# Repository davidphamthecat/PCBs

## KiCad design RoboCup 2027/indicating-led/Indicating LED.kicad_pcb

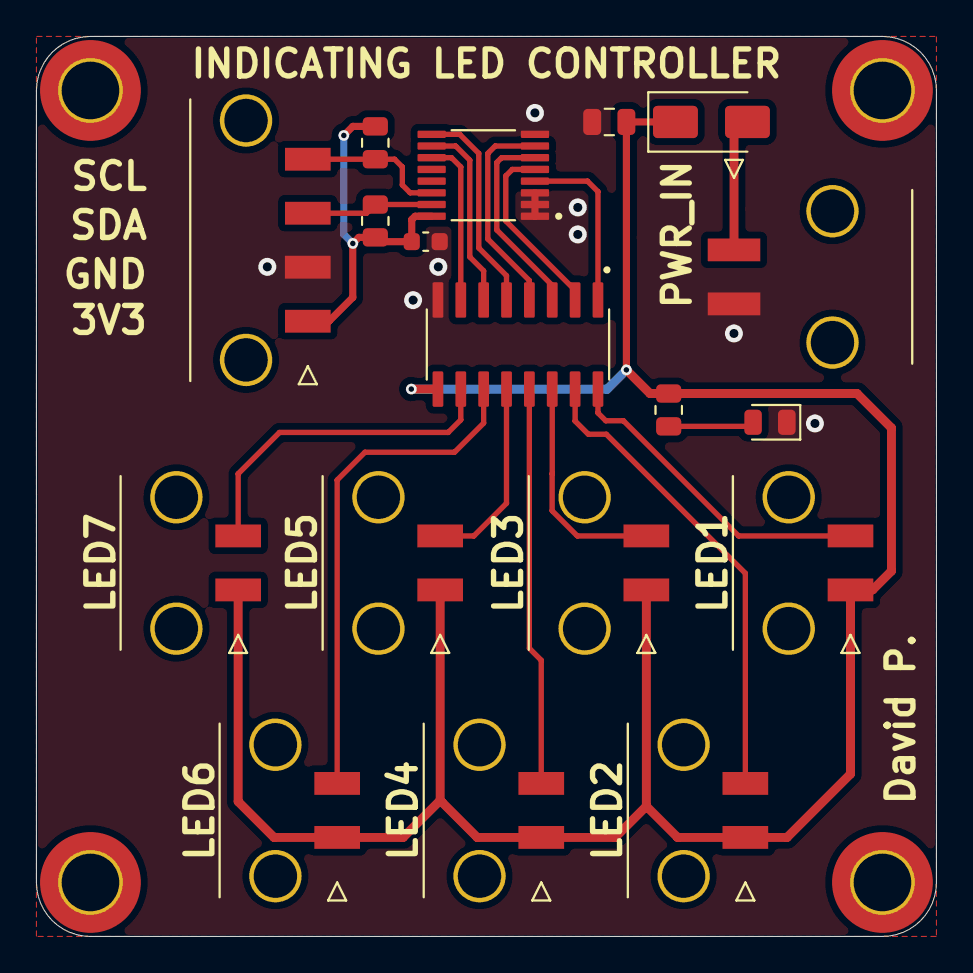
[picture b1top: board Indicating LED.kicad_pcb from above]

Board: 2 copper layers, 50.0 x 50.0 mm, 22 parts (0 on the bottom side), 21 nets.

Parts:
C101: 0.1u; C_0603_1608Metric
C102: 10u; C_0805_2012Metric
D101: LED; LED_0805_2012Metric
D102: SS14; D_SMA
H101, H102, H103, H104: MountingHole_M3; MountingHole_3.2mm_M3_DIN965_Pad_TopBottom
J101: Signal; CONN_Molex-MicroFit-01x04_Vertical
J102: PWR_In; CONN_Molex-MicroFit-01x02_Horizontal
J103, J104, J105, J106, J107, J108, J109: Conn_PWR; CONN_Molex-MicroFit-01x02_Vertical
R101, R102, R103: 4k7; R_0805_2012Metric
U101: TCA9534; IC-TCA9534PWR
U102: IC_ULN2003A; IC-ULN2003A

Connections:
+12V: C102.1, D102.1 (K), J103.+ (Pin_1), J104.+ (Pin_1), J105.+ (Pin_1), J106.+ (Pin_1), J107.+ (Pin_1), J108.+ (Pin_1), J109.+ (Pin_1), R101.2, U102.9 (COM)
/LED1-pwr: J103.- (Pin_2), U102.16 (1C)
/LED1-sig: U101.4 (P0), U102.1 (1B)
/LED2-pwr: J104.- (Pin_2), U102.15 (2C)
/LED2-sig: U101.5 (P1), U102.2 (2B)
/LED3-pwr: J105.- (Pin_2), U102.14 (3C)
/LED3-sig: U101.6 (P2), U102.3 (3B)
/LED4-pwr: J106.- (Pin_2), U102.13 (4C)
/LED4-sig: U101.7 (P3), U102.4 (4B)
/LED5-pwr: J107.- (Pin_2), U102.12 (5C)
/LED5-sig: U101.9 (P4), U102.5 (5B)
/LED6-pwr: J108.- (Pin_2), U102.11 (6C)
/LED6-sig: U101.10 (P5), U102.6 (6B)
/LED7-pwr: J109.- (Pin_2), U102.10 (7C)
/LED7-sig: U101.11 (P6), U102.7 (7B)
/SCL: J101.4, R103.1, U101.14 (SCL)
/SDA: J101.3, R102.1, U101.15 (SDA)
GND: C101.2, C102.2, D101.1, J101.2, J102.- (Pin_2), U101.1 (A0), U101.2 (A1), U101.3 (A2), U101.8 (GND), U102.8 (E)
unnamed: D101.2, R101.1
unnamed: D102.2 (A), J102.+ (Pin_1)
VCC: C101.1, J101.1, R102.2, R103.2, U101.16 (VDD)

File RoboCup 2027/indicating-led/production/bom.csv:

Designator,Footprint,Quantity,Value,LCSC Part #
C101,0603,1,0.1u,C14663
C102,0805,1,10u,C15850
D101,0805,1,LED,C84256
D102,D_SMA,1,SS14,C2480
"H101, H102, H103, H104",MountingHole_3.2mm_M3_DIN965_Pad_TopBottom,4,MountingHole_M3,DNP
J101,CONN_Molex-MicroFit-01x04_Vertical,1,Signal,
J102,CONN_Molex-MicroFit-01x02_Horizontal,1,PWR_In,
"J103, J104, J105, J106, J107, J108, J109",CONN_Molex-MicroFit-01x02_Vertical,7,Conn_PWR,
"R101, R102, R103",0805,3,4k7,C17673
U101,IC-TCA9534PWR,1,TCA9534,C783615
U102,IC-ULN2003A,1,IC_ULN2003A,C7512

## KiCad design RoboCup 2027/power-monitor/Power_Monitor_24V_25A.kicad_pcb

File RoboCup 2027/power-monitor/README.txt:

heloooo, remember when ordering select 2 oz copper

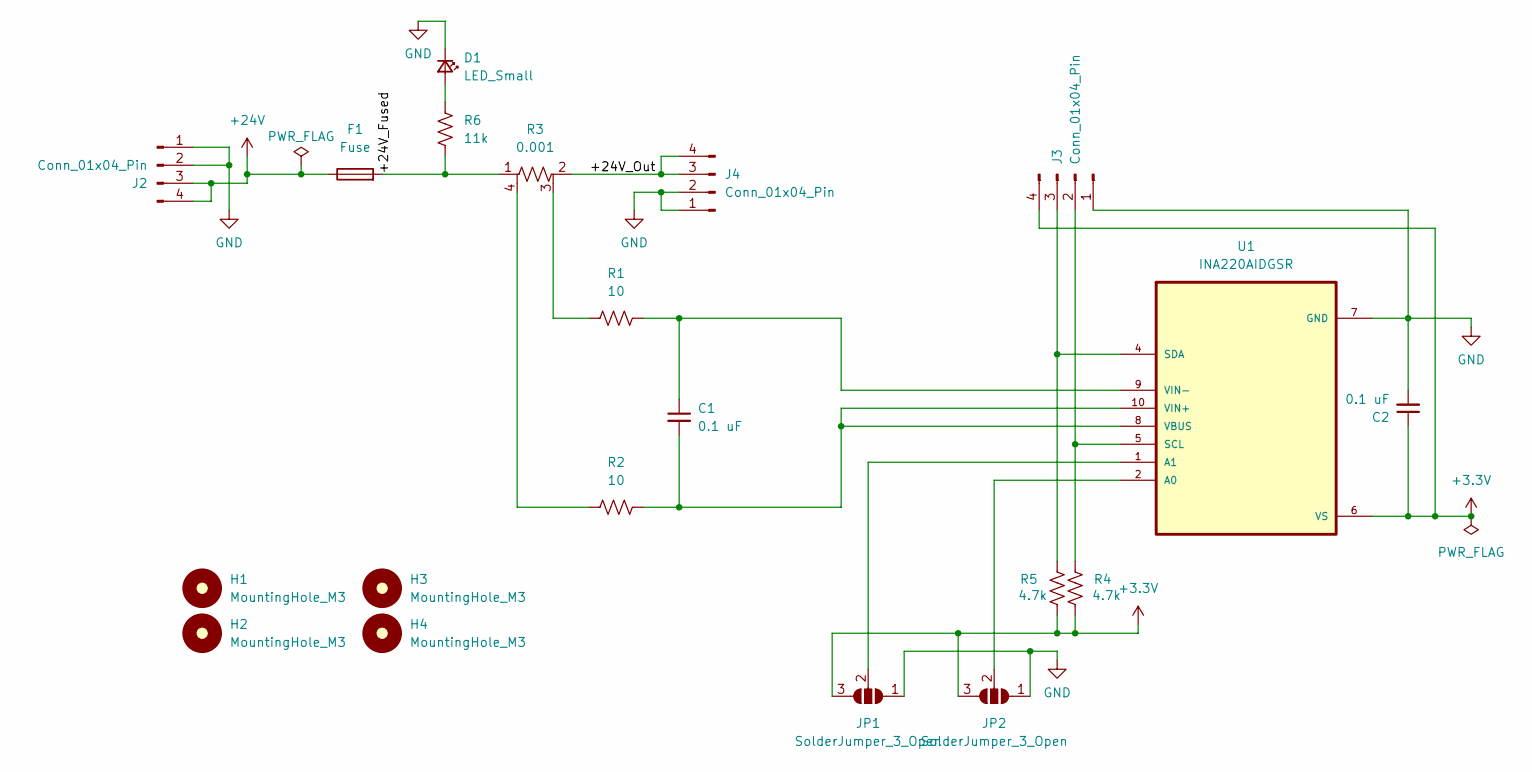
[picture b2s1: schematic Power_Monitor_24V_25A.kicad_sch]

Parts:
C1, C2: 0.1 uF; C_0603_1608Metric
D1: LED_Small; LED_0805_2012Metric
F1: Fuse; Fuseholder_Blade_Mini_Keystone_3568
H1, H2, H3, H4: MountingHole_M3; MountingHole_3.2mm_M3
J2, J3, J4: Conn_01x04_Pin; Molex_Mega-Fit_76829-0004_2x02_P5.70mm_Vertical
JP1, JP2: SolderJumper_3_Open; SolderJumper-3_P1.3mm_Open_RoundedPad1.0x1.5mm
R1, R2: 10; R_0603_1608Metric
R3: 0.001; RESCAF_LVK25-4
R4, R5: 4.7k; R_0603_1608Metric
R6: 11k; R_0603_1608Metric
U1: INA220AIDGSR; SOP50P490X110-10N

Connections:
+3.3V: C2.1, J3.4, JP1.3 (B), JP2.3 (B), R4.1, R5.1, U1.6 (VS)
+24V: F1.1, J2.3, J2.4
/+24V_Fused: F1.2, R3.1, R6.1
/+24V_Out: J4.3, J4.4, R3.2
GND: C2.2, D1.1 (K), J2.1, J2.2, J3.1, J4.1, J4.2, JP1.1 (A), JP2.1 (A), U1.7 (GND)
unnamed: D1.2 (A), R6.2
unnamed: J3.2, R4.2, U1.5 (SCL)
unnamed: J3.3, R5.2, U1.4 (SDA)
unnamed: JP1.2 (C), U1.1 (A1)
unnamed: JP2.2 (C), U1.2 (A0)
unnamed: R1.1, R3.3
unnamed: R2.1, R3.4
unnamed: C1.2, R2.2, U1.8 (VBUS), U1.10 (VIN+)
unnamed: C1.1, R1.2, U1.9 (VIN-)

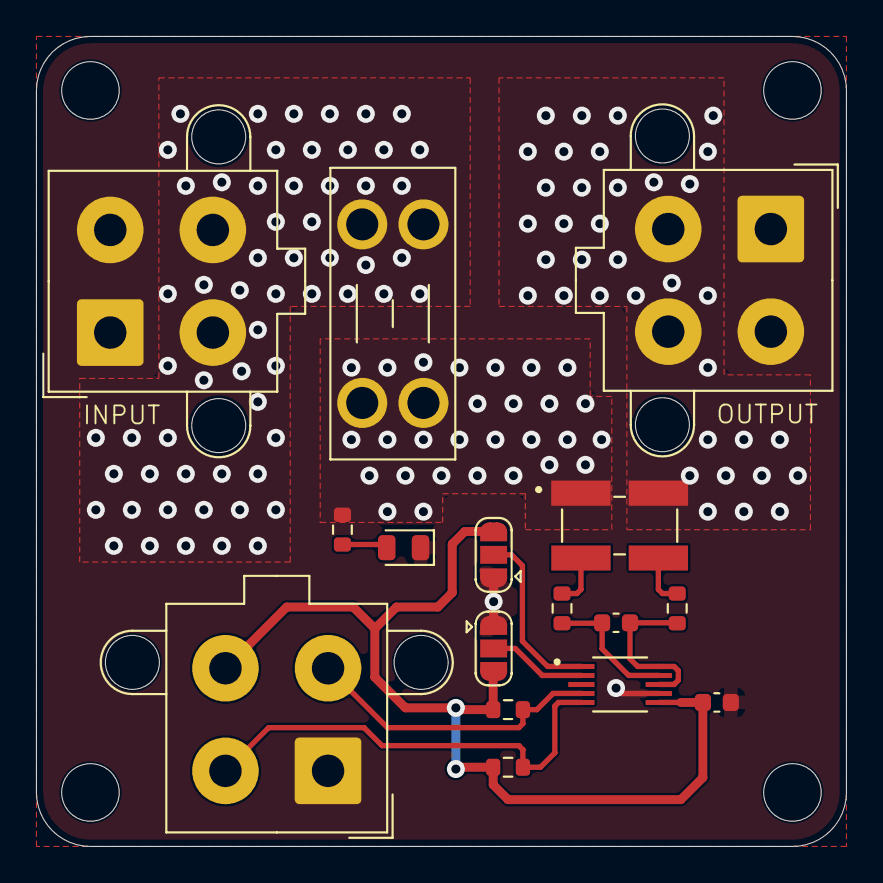
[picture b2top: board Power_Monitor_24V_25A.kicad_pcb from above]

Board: 2 copper layers, 45.0 x 45.0 mm, 20 parts (0 on the bottom side), 14 nets.

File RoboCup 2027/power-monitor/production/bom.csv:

Designator,Footprint,Quantity,Value,LCSC Part #
"C1, C2",0603,2,0.1 uF,
D1,0805,1,LED_Small,
F1,Fuseholder_Blade_Mini_Keystone_3568,1,Fuse,
"H1, H2, H3, H4",MountingHole_3.2mm_M3,4,MountingHole_M3,
"J2, J3, J4",Molex_Mega-Fit_76829-0004_2x02_P5.70mm_Vertical,3,Conn_01x04_Pin,
"R1, R2",0603,2,10,
R3,RESCAF_LVK25-4,1,0.001,
"R4, R5",0603,2,4.7k,
R6,0603,1,11k,
U1,SOP50P490X110-10N,1,INA220AIDGSR,

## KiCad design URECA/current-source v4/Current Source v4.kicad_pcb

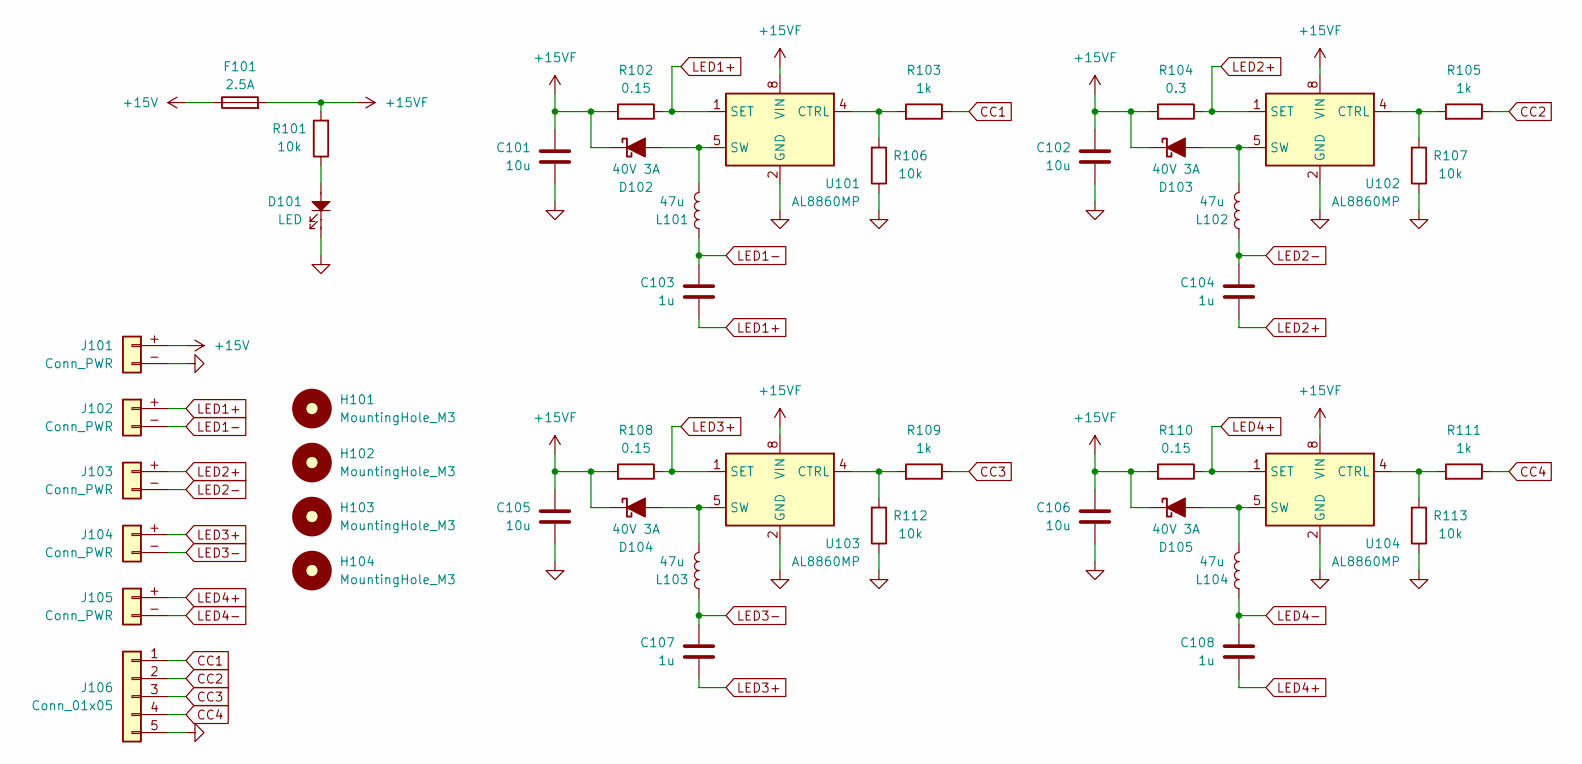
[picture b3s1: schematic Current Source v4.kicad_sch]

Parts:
C101, C102, C105, C106: 10u; C_1206_3216Metric; Part Type Basic; LCSC C70462
C103, C104, C107, C108: 1u; C_0603_1608Metric; Part Type Basic; LCSC C15849
D101: LED; LED_0805_2012Metric; Part Type Basic; LCSC C84256
D102, D103, D104, D105: 40V 3A; D_SMA; Part Type Extended; LCSC C8678
F101: 2.5A; FUSE-MCCQ-122; LCSC DNP
H101, H102, H103, H104: MountingHole_M3; MountingHole_3.2mm_M3_DIN965_Pad_TopBottom; LCSC DNP
J101: Conn_PWR; CONN_XT30U-F_Vertical; LCSC DNP
J102, J103, J104, J105: Conn_PWR; CONN_JST_XH_B2B-XH-AM_1x02_P2.50mm_Vertical; LCSC DNP
J106: Conn_01x05; PinHeader_1x05_P2.54mm_Vertical; LCSC DNP
L101, L102, L103, L104: 47u; L_10.1x10.1_H4.5; Part Type Extended; LCSC C163611
R101, R106, R107, R112, R113: 10k; R_0603_1608Metric; Part Type Basic; LCSC C25804
R102, R108, R110: 0.15; R_1206_3216Metric; Part Type Extended; LCSC C37936
R103, R105, R109, R111: 1k; R_0603_1608Metric; Part Type Basic; LCSC C21190
R104: 0.3; R_1206_3216Metric; Part Type Extended; LCSC C59882
U101, U102, U103, U104: AL8860MP; MSOP-8-1EP_3x3mm_P0.65mm_EP1.5x1.8mm; Part Type Extended; LCSC C500782

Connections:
+15V: F101.1, J101.+ (Pin_1)
+15VF: C101.1, C102.1, C105.1, C106.1, D102.1 (K), D103.1 (K), D104.1 (K), D105.1 (K), F101.2, R101.2, R102.2, R104.2, R108.2, R110.2, U101.8 (VIN), U102.8 (VIN), U103.8 (VIN), U104.8 (VIN)
CC1: J106.1, R103.1
CC2: J106.2, R105.1
CC3: J106.3, R109.1
CC4: J106.4, R111.1
GND: C101.2, C102.2, C105.2, C106.2, D101.1, J101.- (Pin_2), J106.5, R106.1, R107.1, R112.1, R113.1, U101.2 (GND), U101.3 (GND), U101.9 (GND), U102.2 (GND), U102.3 (GND), U102.9 (GND), U103.2 (GND), U103.3 (GND), U103.9 (GND), U104.2 (GND), U104.3 (GND), U104.9 (GND)
LED1+: C103.2, J102.+ (Pin_1), R102.1, U101.1 (SET)
LED1-: C103.1, J102.- (Pin_2), L101.1
LED2+: C104.2, J103.+ (Pin_1), R104.1, U102.1 (SET)
LED2-: C104.1, J103.- (Pin_2), L102.1
LED3+: C107.2, J104.+ (Pin_1), R108.1, U103.1 (SET)
LED3-: C107.1, J104.- (Pin_2), L103.1
LED4+: C108.2, J105.+ (Pin_1), R110.1, U104.1 (SET)
LED4-: C108.1, J105.- (Pin_2), L104.1
unnamed: D101.2, R101.1
unnamed: D102.2 (A), L101.2, U101.5 (SW), U101.6 (SW)
unnamed: D103.2 (A), L102.2, U102.5 (SW), U102.6 (SW)
unnamed: D104.2 (A), L103.2, U103.5 (SW), U103.6 (SW)
unnamed: D105.2 (A), L104.2, U104.5 (SW), U104.6 (SW)
unnamed: R103.2, R106.2, U101.4 (CTRL)
unnamed: R105.2, R107.2, U102.4 (CTRL)
unnamed: R109.2, R112.2, U103.4 (CTRL)
unnamed: R111.2, R113.2, U104.4 (CTRL)

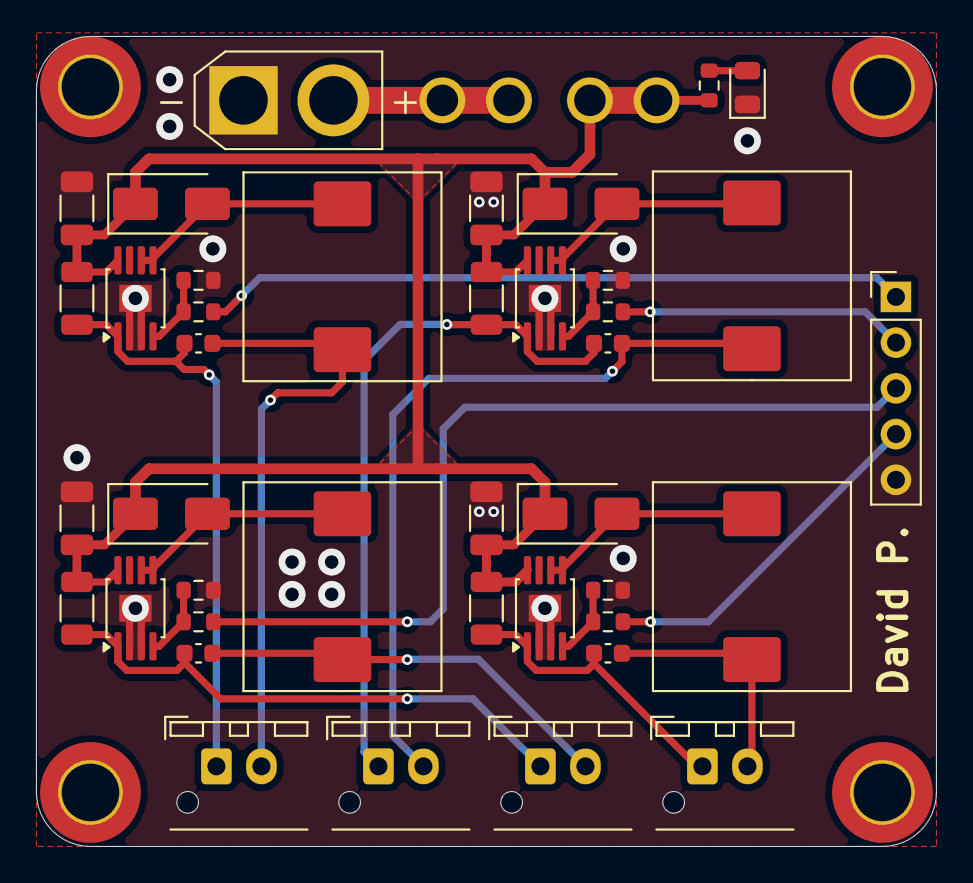
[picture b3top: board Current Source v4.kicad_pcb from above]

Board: 2 copper layers, 50.0 x 45.0 mm, 45 parts (0 on the bottom side), 24 nets.

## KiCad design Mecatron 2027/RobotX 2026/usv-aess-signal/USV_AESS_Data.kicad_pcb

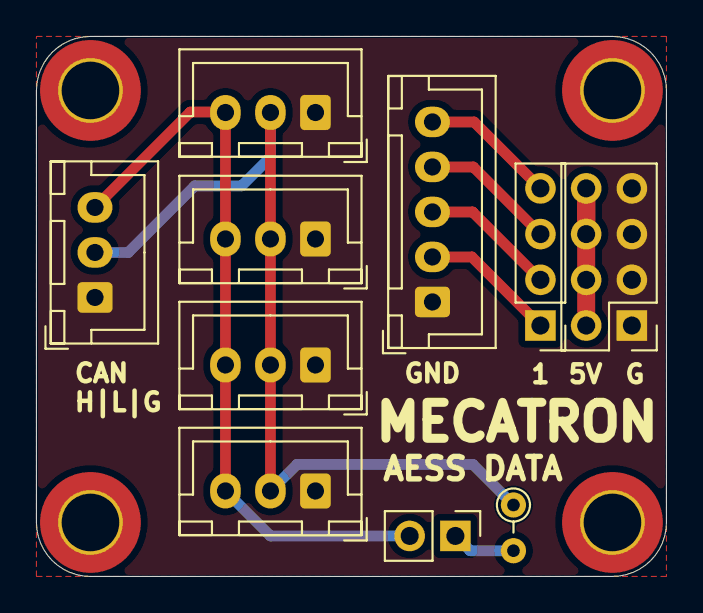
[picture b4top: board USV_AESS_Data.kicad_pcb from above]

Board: 2 copper layers, 35.0 x 30.0 mm, 14 parts (0 on the bottom side), 9 nets.

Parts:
H101, H102, H103, H104: MountingHole_M3; MountingHole_3.2mm_M3_DIN965_Pad_TopBottom
J101, J102, J103, J104, J105: CAN; JST_XH_B3B-XH-A_1x03_P2.50mm_Vertical
J106: PWM +/-; PinHeader_2x04_P2.54mm_Vertical
J107: PWM; PinHeader_1x04_P2.54mm_Vertical
J108: PWM_Out; JST_XH_B5B-XH-A_1x05_P2.50mm_Vertical
J109: Conn_01x02; PinHeader_1x02_P2.54mm_Vertical
R101: 120; R_Axial_DIN0204_L3.6mm_D1.6mm_P2.54mm_Vertical

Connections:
+5V: J106.2, J106.4, J106.6, J106.8
/CAN_H: J101.3, J102.3, J103.3, J104.3, J105.3, J109.2
/CAN_L: J101.2, J102.2, J103.2, J104.2, J105.2, R101.1
/PWM-01: J107.1, J108.2
/PWM-02: J107.2, J108.3
/PWM-03: J107.3, J108.4
/PWM-04: J107.4, J108.5
GND: J101.1, J102.1, J103.1, J104.1, J105.1, J106.1, J106.3, J106.5, J106.7, J108.1
unnamed: J109.1, R101.2

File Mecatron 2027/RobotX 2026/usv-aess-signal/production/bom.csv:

Designator,Footprint,Quantity,Value,LCSC Part #
"H101, H102, H103, H104",MountingHole_3.2mm_M3_DIN965_Pad_TopBottom,4,MountingHole_M3,
"J101, J102, J103, J104, J105",JST_XH_B3B-XH-A_1x03_P2.50mm_Vertical,5,CAN,
J106,PinHeader_2x04_P2.54mm_Vertical,1,PWM +/-,
J107,PinHeader_1x04_P2.54mm_Vertical,1,PWM,
J108,JST_XH_B5B-XH-A_1x05_P2.50mm_Vertical,1,PWM_Out,
J109,PinHeader_1x02_P2.54mm_Vertical,1,Conn_01x02,
R101,R_Axial_DIN0204_L3.6mm_D1.6mm_P2.54mm_Vertical,1,120,

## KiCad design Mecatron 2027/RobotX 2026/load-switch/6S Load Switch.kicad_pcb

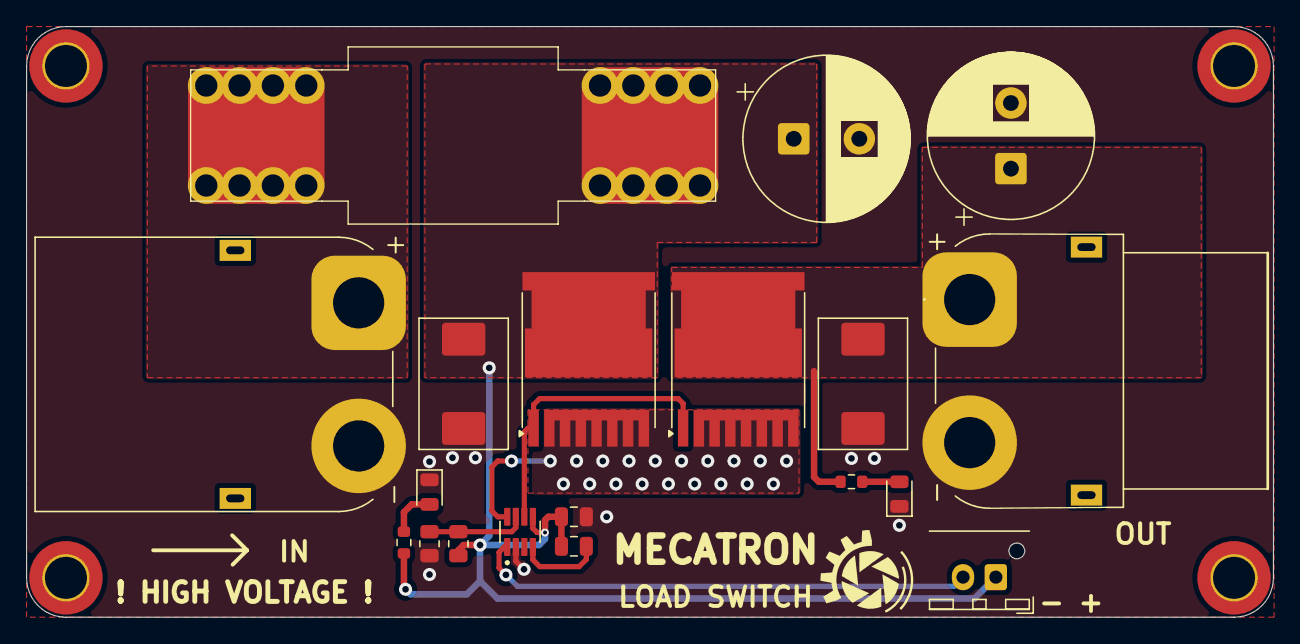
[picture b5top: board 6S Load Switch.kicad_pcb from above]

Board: 4 copper layers, 95.0 x 45.0 mm, 23 parts (0 on the bottom side), 11 nets.

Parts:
C101, C102: 620u 50V; CP_Radial_D12.5mm_P5.00mm
C103, C104: 1u; C_0805_2012Metric
D101, D102: SMCJ33CA; D_SMC_TVS
D103, D104: LED; LED_0805_2012Metric
F101: 60A; FUSE-MIDI-STANDOFF_BUTR_0850_NO_HOLE
H101, H102, H103, H104: MountingHole_M3; MountingHole_3.2mm_M3_DIN965_Pad_TopBottom
J101: XT90M; CONN_XT90PW-M_Horizontal
J102: XT90F; CONN_XT90PW-F_Horizontal
J103: Conn_EN; CONN_JST_XH_B2B-XH-AM_1x02_P2.50mm_Vertical
Q101, Q102: IPT015N10N5; Infineon_PG-HSOF-8-1
R101, R102: 5k1; R_0603_1608Metric
R103: 220k; R_0805_2012Metric
R104: 10k; R_0805_2012Metric
U101: LM74502DDFR; IC-LM74502

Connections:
+25V2: F101.1, J101.+ (Pin_1)
+25V2F: C101.1, C103.1, C104.1, D101.2 (A), F101.2, J103.+ (Pin_1), Q101.3 (D), R101.2, R103.2, U101.5 (VS)
+25V2FO: C102.1, D102.2 (A), J102.+ (Pin_1), Q102.3 (D), R102.2
/PWR_EN: J103.- (Pin_2), U101.1 (EN/UVLO)
GND: C101.2, C102.2, C104.2, D101.1 (K), D102.1 (K), D103.1, D104.1, J101.- (Pin_2), J102.- (Pin_2), R104.1, U101.2 (GND)
unnamed: D103.2, R101.1
unnamed: D104.2, R102.1
unnamed: Q101.1 (G), Q102.1 (G), U101.6 (GATE)
unnamed: Q101.2 (S), Q102.2 (S), U101.8 (SRC)
unnamed: R103.1, R104.2, U101.7 (OV)
unnamed: C103.2, U101.4 (VCAP)

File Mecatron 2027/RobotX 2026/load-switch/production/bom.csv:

Designator,Footprint,Quantity,Value,LCSC Part #
"C101, C102",CP_Radial_D12.5mm_P5.00mm,2,620u 50V,
"C103, C104",0805,2,1u,C28323
"D101, D102",D_SMC_TVS,2,SMCJ33CA,C310048
"D103, D104",0805,2,LED,C84256
F101,FUSE-MIDI-STANDOFF_BUTR_0850_NO_HOLE,1,60A,
"H101, H102, H103, H104",MountingHole_3.2mm_M3_DIN965_Pad_TopBottom,4,MountingHole_M3,
J101,CONN_XT90PW-M_Horizontal,1,XT90M,
J102,CONN_XT90PW-F_Horizontal,1,XT90F,
J103,CONN_JST_XH_B2B-XH-AM_1x02_P2.50mm_Vertical,1,Conn_EN,
"Q101, Q102",Infineon_PG-HSOF-8-1,2,IPT015N10N5,C108964
"R101, R102",0603,2,5k1,C23186
R103,0805,1,220k,C17556
R104,0805,1,10k,C17414
U101,IC-LM74502,1,LM74502DDFR,C3236215

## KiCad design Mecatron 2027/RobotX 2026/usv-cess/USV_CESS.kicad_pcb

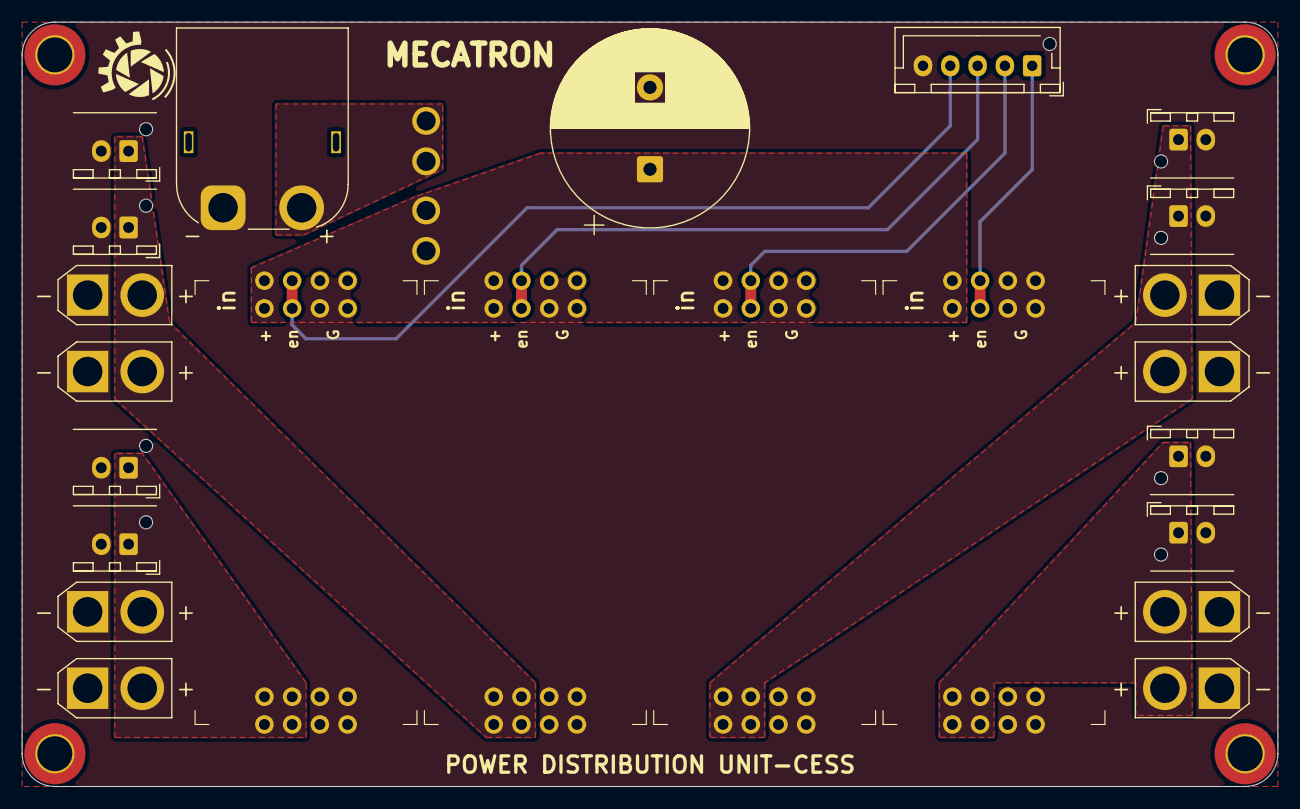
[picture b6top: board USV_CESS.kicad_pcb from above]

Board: 2 copper layers, 115.0 x 70.0 mm, 28 parts (0 on the bottom side), 11 nets.

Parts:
C101: 1000u; CP_Radial_D18.0mm_P7.50mm
F101: 40A; FUSE-MCCQ-122
H101, H102, H103, H104: MountingHole_M3; MountingHole_3.2mm_M3_DIN965_Pad_TopBottom
J101: XT60M; CONN_XT60PW-M_Horizontal
J102: EN; JST_XH_B5B-XH-AM_1x05_P2.50mm_Vertical
J103, J104, J107, J108, J111, J112, J115, J116: JST_XH; CONN_JST_XH_B2B-XH-AM_1x02_P2.50mm_Vertical
J105, J106, J109, J110, J113, J114, J117, J118: XT30; CONN_XT30U-F_Vertical
U101: Output 1; CUS-TPS54560 KangWeiTech
U102: Output 2; CUS-TPS54560 KangWeiTech
U103: Output 3; CUS-TPS54560 KangWeiTech
U104: Output 4; CUS-TPS54560 KangWeiTech

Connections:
+25V2: F101.1, J101.+ (Pin_1)
+25V2F: C101.1, F101.2, U101.1 (V_{IN}), U102.1 (V_{IN}), U103.1 (V_{IN}), U104.1 (V_{IN})
/EN_1: J102.1, U101.EN
/EN_2: J102.2, U102.EN
/EN_3: J102.3, U103.EN
/EN_4: J102.4, U104.EN
GND: C101.2, J101.- (Pin_2), J102.5, J103.- (Pin_2), J104.- (Pin_2), J105.- (Pin_2), J106.- (Pin_2), J107.- (Pin_2), J108.- (Pin_2), J109.- (Pin_2), J110.- (Pin_2), J111.- (Pin_2), J112.- (Pin_2), J113.- (Pin_2), J114.- (Pin_2), J115.- (Pin_2), J116.- (Pin_2), J117.- (Pin_2), J118.- (Pin_2), U101.G (GND), U102.G (GND), U103.G (GND), U104.G (GND)
Output 1: J103.+ (Pin_1), J104.+ (Pin_1), J105.+ (Pin_1), J106.+ (Pin_1), U101.2 (V_{OUT})
Output 2: J107.+ (Pin_1), J108.+ (Pin_1), J109.+ (Pin_1), J110.+ (Pin_1), U102.2 (V_{OUT})
Output 3: J111.+ (Pin_1), J112.+ (Pin_1), J113.+ (Pin_1), J114.+ (Pin_1), U103.2 (V_{OUT})
Output 4: J115.+ (Pin_1), J116.+ (Pin_1), J117.+ (Pin_1), J118.+ (Pin_1), U104.2 (V_{OUT})

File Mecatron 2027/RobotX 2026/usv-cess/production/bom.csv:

Designator,Footprint,Quantity,Value,LCSC Part #
C101,CP_Radial_D18.0mm_P7.50mm,1,1000u,C724666
F101,FUSE-MCCQ-122,1,40A,
"H101, H102, H103, H104",MountingHole_3.2mm_M3_DIN965_Pad_TopBottom,4,MountingHole_M3,
J101,CONN_XT60PW-M_Horizontal,1,XT60M,
J102,JST_XH_B5B-XH-AM_1x05_P2.50mm_Vertical,1,EN,
"J103, J104, J107, J108, J111, J112, J115, J116",CONN_JST_XH_B2B-XH-AM_1x02_P2.50mm_Vertical,8,JST_XH,
"J105, J106, J109, J110, J113, J114, J117, J118",CONN_XT30U-F_Vertical,8,XT30,
U101,CUS-TPS54560 KangWeiTech,1,Output 1,
U102,CUS-TPS54560 KangWeiTech,1,Output 2,
U103,CUS-TPS54560 KangWeiTech,1,Output 3,
U104,CUS-TPS54560 KangWeiTech,1,Output 4,

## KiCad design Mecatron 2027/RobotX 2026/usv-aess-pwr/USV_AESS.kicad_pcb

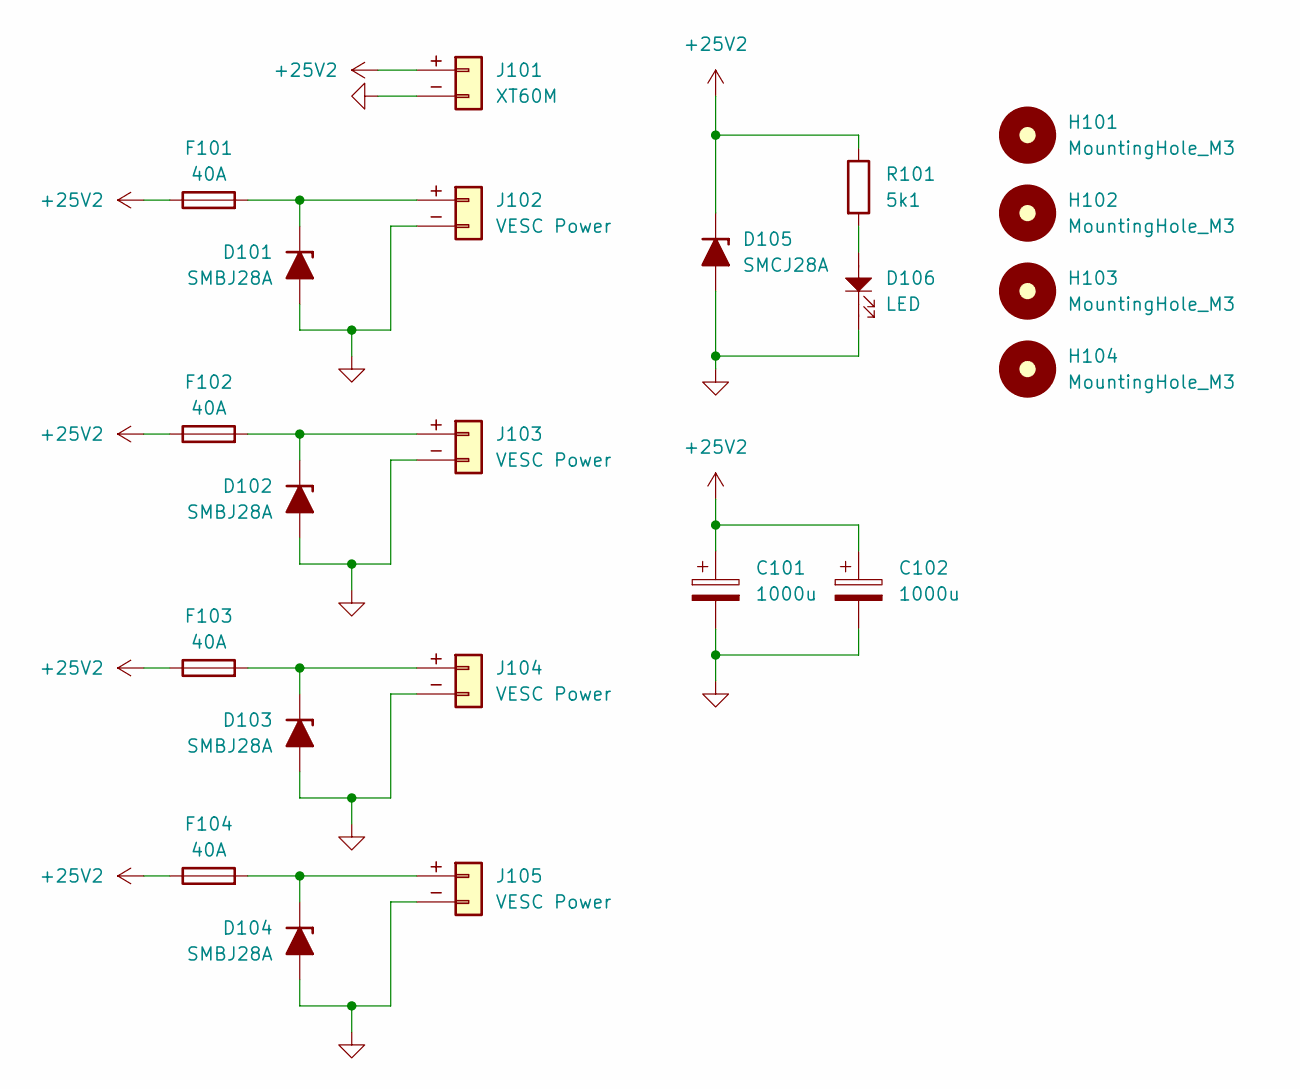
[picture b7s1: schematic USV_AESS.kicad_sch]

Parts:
C101, C102: 1000u; CP_Radial_D16.0mm_P7.50mm; Part Type Taobao
D101, D102, D103, D104: SMBJ28A; D_SMB; Part Type Extended
D105: SMCJ28A; D_SMC; Part Type Extended; LCSC C10250
D106: LED; LED_0805_2012Metric; Part Type Basic; LCSC C84256
F101, F102, F103, F104: 40A; FUSE-MCCQ-122; Part Type DNP
H101, H102, H103, H104: MountingHole_M3; MountingHole_3.2mm_M3_DIN965_Pad_TopBottom; Part Type DNP
J101: XT60M; CONN_XT60PW-M_Horizontal; Part Type DNP
J102, J103, J104, J105: VESC Power; CONN_XT60-F_Vertical; Part Type DNP
R101: 5k1; R_1206_3216Metric; Part Type Extended; LCSC C881294

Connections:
+25V2: C101.1, C102.1, D105.1 (K), F101.1, F102.1, F103.1, F104.1, J101.+ (Pin_1), R101.1
GND: C101.2, C102.2, D101.2 (A), D102.2 (A), D103.2 (A), D104.2 (A), D105.2 (A), D106.1, J101.- (Pin_2), J102.- (Pin_2), J103.- (Pin_2), J104.- (Pin_2), J105.- (Pin_2)
unnamed: D101.1 (K), F101.2, J102.+ (Pin_1)
unnamed: D102.1 (K), F102.2, J103.+ (Pin_1)
unnamed: D103.1 (K), F103.2, J104.+ (Pin_1)
unnamed: D104.1 (K), F104.2, J105.+ (Pin_1)
unnamed: D106.2, R101.2

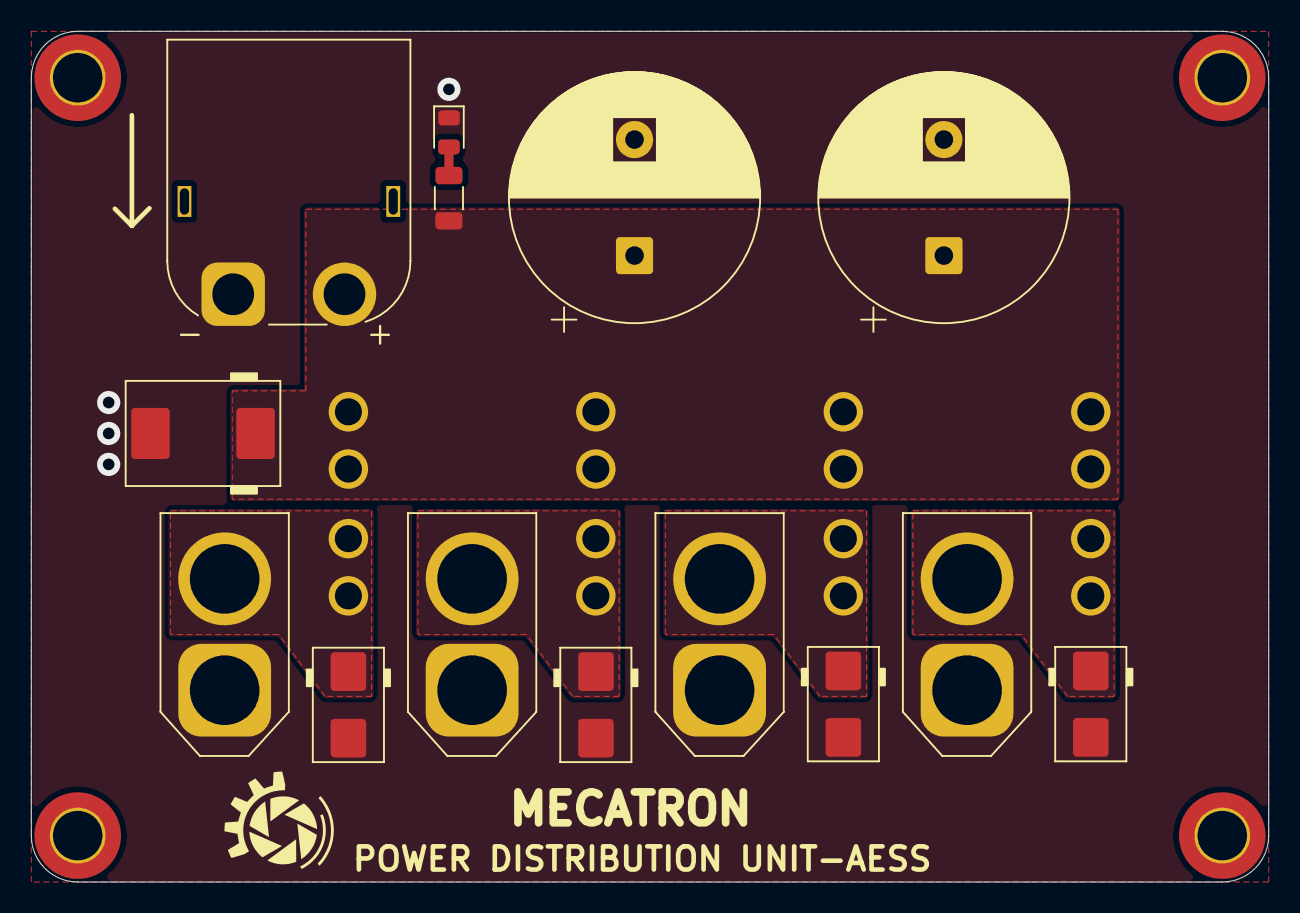
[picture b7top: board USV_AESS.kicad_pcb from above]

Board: 2 copper layers, 80.0 x 55.0 mm, 22 parts (0 on the bottom side), 7 nets.

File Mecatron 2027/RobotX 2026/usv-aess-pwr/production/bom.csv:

Designator,Footprint,Quantity,Value,LCSC Part #
"C101, C102",CP_Radial_D16.0mm_P7.50mm,2,1000u,
"D101, D102, D103, D104",D_SMB,4,SMBJ28A,
D105,D_SMC,1,SMCJ28A,C10250
D106,0805,1,LED,C84256
"F101, F102, F103, F104",FUSE-MCCQ-122,4,40A,
"H101, H102, H103, H104",MountingHole_3.2mm_M3_DIN965_Pad_TopBottom,4,MountingHole_M3,
J101,CONN_XT60PW-M_Horizontal,1,XT60M,
"J102, J103, J104, J105",CONN_XT60-F_Vertical,4,VESC Power,
R101,1206,1,5k1,C881294

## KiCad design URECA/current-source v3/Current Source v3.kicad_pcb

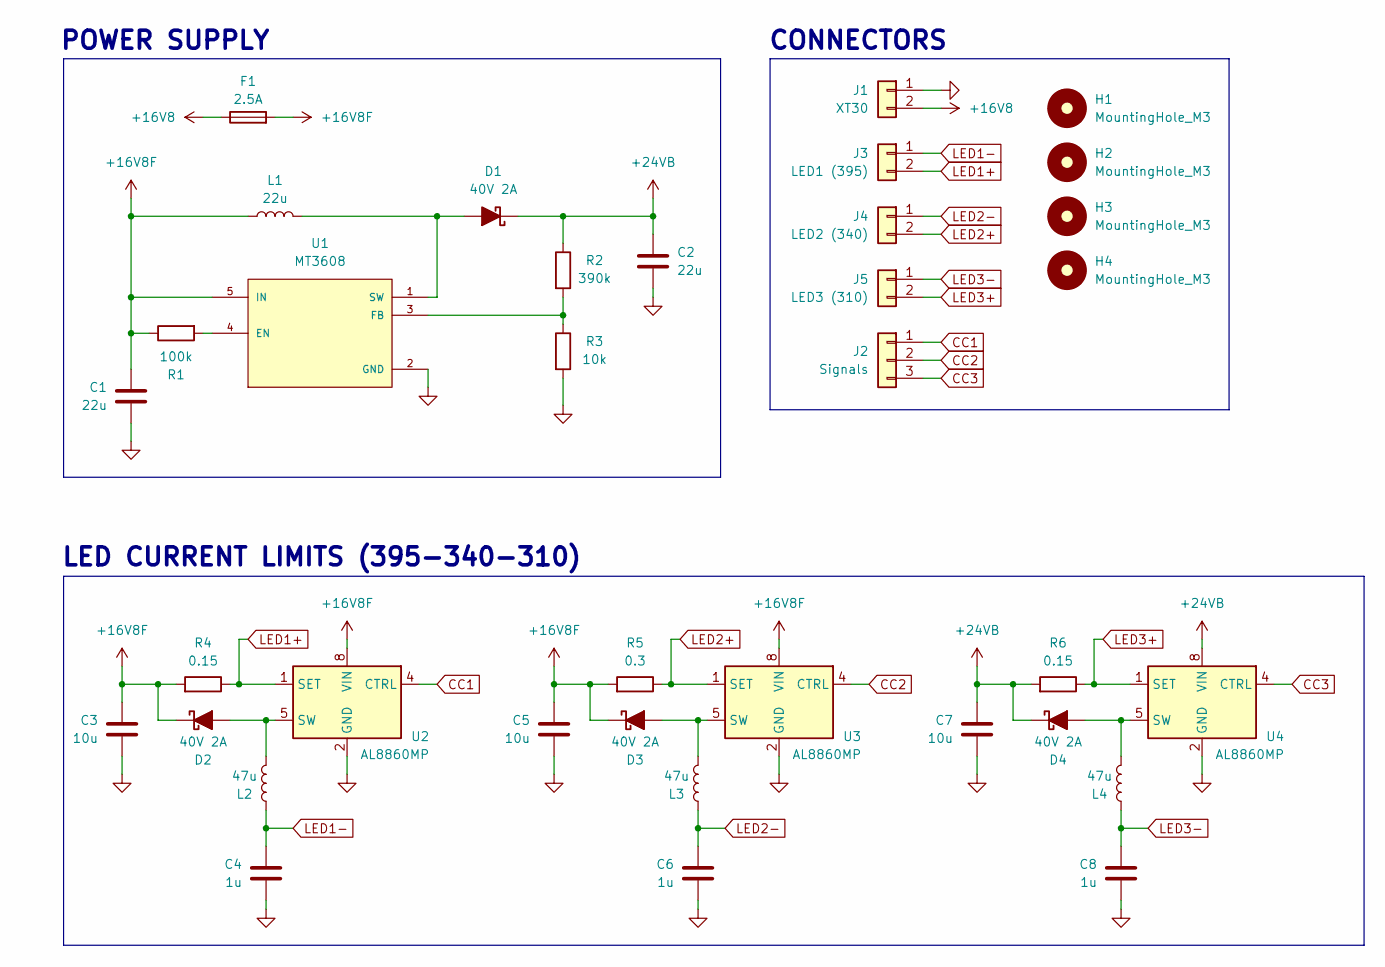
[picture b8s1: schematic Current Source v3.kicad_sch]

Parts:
C1, C2: 22u; C_0805_2012Metric; Part Type Basic; LCSC C45783
C3, C5, C7: 10u; C_0805_2012Metric; Part Type Basic; LCSC C15850
C4, C6, C8: 1u; C_0805_2012Metric; Part Type Basic; LCSC C28323
D1, D2, D3, D4: 40V 2A; D_SMA; Part Type Extended; LCSC C92506
F1: 2.5A; Fuse_1206_3216Metric; Part Type Extended; LCSC C187599
H1, H2, H3, H4: MountingHole_M3; MountingHole_3.2mm_M3_DIN965_Pad_TopBottom; LCSC DNP
J1: XT30; AMASS_XT30U-M_1x02_P5.0mm_Vertical; LCSC DNP
J2: Signals; PinHeader_1x03_P1.00mm_Vertical; LCSC DNP
J3: LED1 (395); JST_XH_B2B-XH-A_1x02_P2.50mm_Vertical; LCSC DNP
J4: LED2 (340); JST_XH_B2B-XH-A_1x02_P2.50mm_Vertical; LCSC DNP
J5: LED3 (310); JST_XH_B2B-XH-A_1x02_P2.50mm_Vertical; LCSC DNP
L1: 22u; IND_MSS7341-223MLD; Part Type Extended; LCSC C3911449
L2, L3, L4: 47u; 46473C; Part Type Extended; LCSC C6689096
R1: 100k; R_0805_2012Metric; Part Type Basic; LCSC C149504
R2: 390k; R_0805_2012Metric; Part Type Extended; LCSC C17656
R3: 10k; R_0805_2012Metric; Part Type Basic; LCSC C17414
R4, R6: 0.15; R_1206_3216Metric; Part Type Basic; LCSC C1015
R5: 0.3; R_1206_3216Metric; Part Type Extended; LCSC C28319
U1: MT3608; SOT95P280X145-6N; PARTREV 1.0; LCSC C84817
U2, U3, U4: AL8860MP; MSOP-8-1EP_3x3mm_P0.65mm_EP1.5x1.8mm; Part Type Extended; LCSC C500782

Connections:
+16V8: F1.1, J1.2
+16V8F: C1.1, C3.1, C5.1, D2.1 (K), D3.1 (K), F1.2, L1.1, R1.1, R4.2, R5.2, U1.5 (IN), U2.8 (VIN), U3.8 (VIN)
+24VB: C2.1, C7.1, D1.1 (K), D4.1 (K), R2.1, R6.2, U4.8 (VIN)
CC1: J2.1, U2.4 (CTRL)
CC2: J2.2, U3.4 (CTRL)
CC3: J2.3, U4.4 (CTRL)
GND: C1.2, C2.2, C3.2, C4.2, C5.2, C6.2, C7.2, C8.2, J1.1, R3.2, U1.2 (GND), U2.2 (GND), U2.3 (GND), U2.9 (GND), U3.2 (GND), U3.3 (GND), U3.9 (GND), U4.2 (GND), U4.3 (GND), U4.9 (GND)
LED1+: J3.2, R4.1, U2.1 (SET)
LED1-: C4.1, J3.1, L2.1
LED2+: J4.2, R5.1, U3.1 (SET)
LED2-: C6.1, J4.1, L3.1
LED3+: J5.2, R6.1, U4.1 (SET)
LED3-: C8.1, J5.1, L4.1
unnamed: D1.2 (A), L1.2, U1.1 (SW)
unnamed: D2.2 (A), L2.2, U2.5 (SW), U2.6 (SW)
unnamed: D3.2 (A), L3.2, U3.5 (SW), U3.6 (SW)
unnamed: D4.2 (A), L4.2, U4.5 (SW), U4.6 (SW)
unnamed: R1.2, U1.4 (EN)
unnamed: R2.2, R3.1, U1.3 (FB)

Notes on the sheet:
LED CURRENT LIMITS (395-340-310)
CONNECTORS
POWER SUPPLY

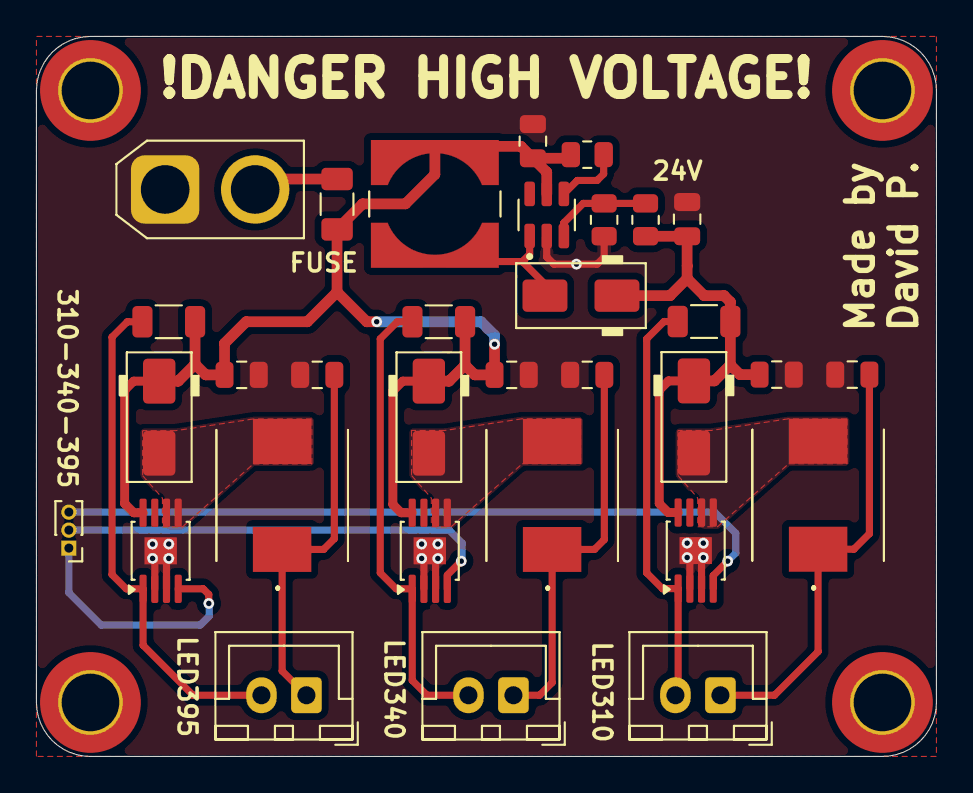
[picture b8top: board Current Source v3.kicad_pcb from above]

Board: 2 copper layers, 50.0 x 40.0 mm, 36 parts (0 on the bottom side), 19 nets.

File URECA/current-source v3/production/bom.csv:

Designator,Footprint,Quantity,Value,LCSC Part #
"C1, C2",0805,2,22u,C45783
"C3, C5, C7",0805,3,10u,C15850
"C4, C6, C8",0805,3,1u,C28323
"D1, D2, D3, D4",D_SMA,4,40V 2A,C92506
F1,1206,1,2.5A,C187599
"H1, H2, H3, H4",MountingHole_3.2mm_M3_DIN965_Pad_TopBottom,4,MountingHole_M3,DNP
J1,AMASS_XT30U-M_1x02_P5.0mm_Vertical,1,XT30,DNP
J2,PinHeader_1x03_P1.00mm_Vertical,1,Signals,DNP
J3,JST_XH_B2B-XH-A_1x02_P2.50mm_Vertical,1,LED1 (395),DNP
J4,JST_XH_B2B-XH-A_1x02_P2.50mm_Vertical,1,LED2 (340),DNP
J5,JST_XH_B2B-XH-A_1x02_P2.50mm_Vertical,1,LED3 (310),DNP
L1,IND_MSS7341-223MLD,1,22u,C3911449
"L2, L3, L4",46473C,3,47u,C6689096
R1,0805,1,100k,C149504
R2,0805,1,390k,C17656
R3,0805,1,10k,C17414
"R4, R6",1206,2,0.15,C1015
R5,1206,1,0.3,C28319
U1,SOT95P280X145-6N,1,MT3608,C84817
"U2, U3, U4",MSOP-8-1EP_3x3mm_P0.65mm_EP1.5x1.8mm,3,AL8860MP,C500782
